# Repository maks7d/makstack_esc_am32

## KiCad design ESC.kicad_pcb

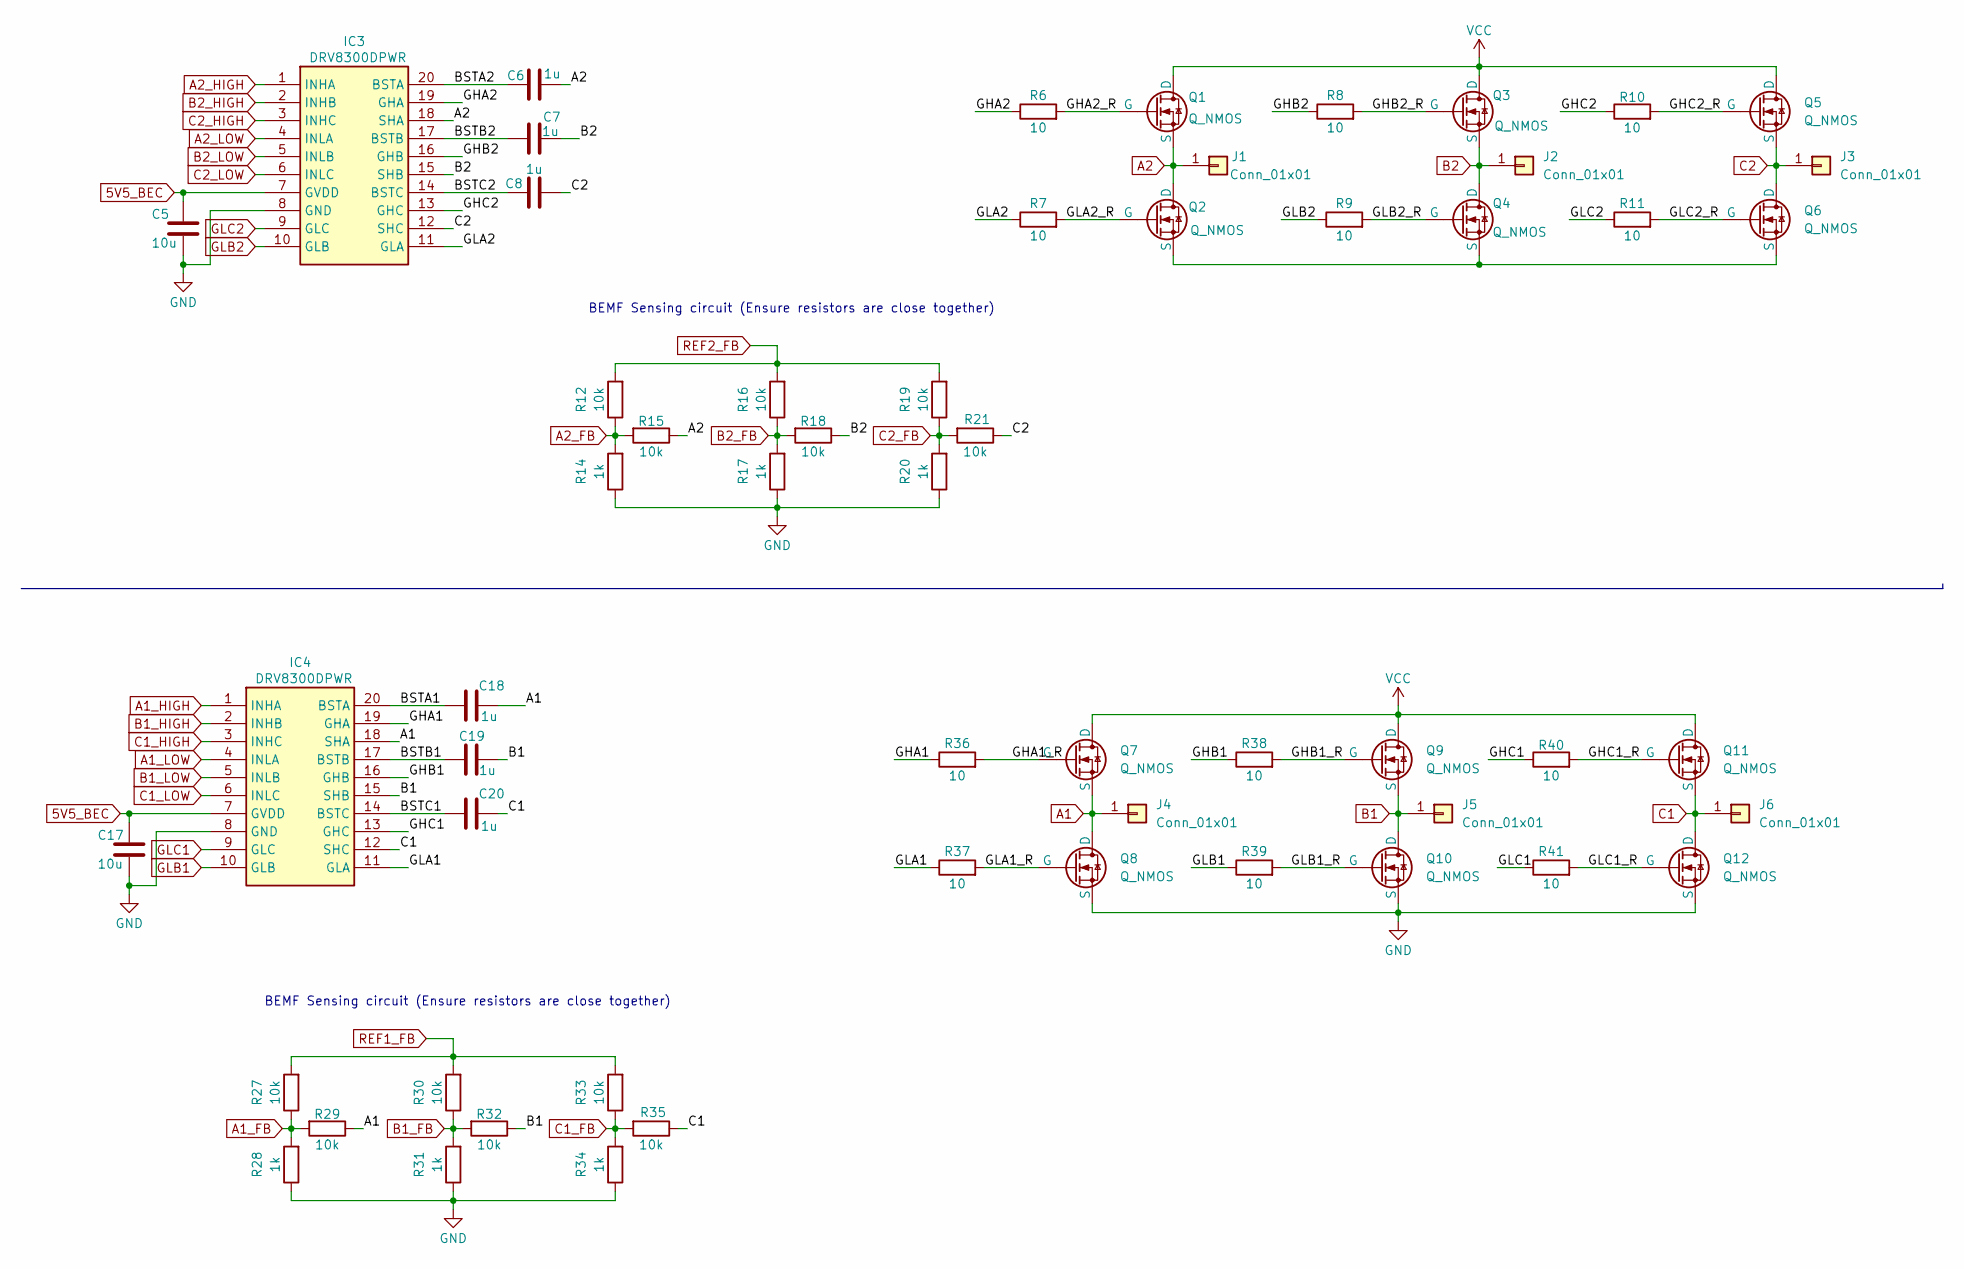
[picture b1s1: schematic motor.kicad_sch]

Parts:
C5, C17: 10u; C_0402_1005Metric
C6, C7, C8, C18, C19, C20: 1u; C_0402_1005Metric
IC3, IC4: DRV8300DPWR; SOP65P640X120-20M; Mouser Part Number 595-DRV8300DPWR
J1, J2, J3, J4, J5, J6: Conn_01x01; TestPoint_Pad_2.0x2.0mm
Q1, Q2, Q3, Q4, Q5, Q6, Q7, Q8, Q9, Q10, Q11, Q12: Q_NMOS; TRANS_NTMFS5C628NLT1G
R6, R7, R8, R9, R10, R11, R36, R37, R38, R39, R40, R41: 10; R_0402_1005Metric
R12, R15, R16, R18, R19, R21, R27, R29, R30, R32, R33, R35: 10k; R_0402_1005Metric
R14, R17, R20, R28, R31, R34: 1k; R_0402_1005Metric

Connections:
5V5_BEC: C5.1, C17.1, IC3.7 (GVDD), IC4.7 (GVDD); also elsewhere on the board
/Motor1-2/BSTA1: C18.1, IC4.20 (BSTA)
/Motor1-2/BSTA2: C6.1, IC3.20 (BSTA)
/Motor1-2/BSTB1: C19.1, IC4.17 (BSTB)
/Motor1-2/BSTB2: C7.1, IC3.17 (BSTB)
/Motor1-2/BSTC1: C20.1, IC4.14 (BSTC)
/Motor1-2/BSTC2: C8.1, IC3.14 (BSTC)
/Motor1-2/GHA1: IC4.19 (GHA), R36.1
/Motor1-2/GHA1_R: Q7.G, R36.2
/Motor1-2/GHA2: IC3.19 (GHA), R6.1
/Motor1-2/GHA2_R: Q1.G, R6.2
/Motor1-2/GHB1: IC4.16 (GHB), R38.1
/Motor1-2/GHB1_R: Q9.G, R38.2
/Motor1-2/GHB2: IC3.16 (GHB), R8.1
/Motor1-2/GHB2_R: Q3.G, R8.2
/Motor1-2/GHC1: IC4.13 (GHC), R40.1
/Motor1-2/GHC1_R: Q11.G, R40.2
/Motor1-2/GHC2: IC3.13 (GHC), R10.1
/Motor1-2/GHC2_R: Q5.G, R10.2
/Motor1-2/GLA1: IC4.11 (GLA), R37.1
/Motor1-2/GLA1_R: Q8.G, R37.2
/Motor1-2/GLA2: IC3.11 (GLA), R7.1
/Motor1-2/GLA2_R: Q2.G, R7.2
/Motor1-2/GLB1_R: Q10.G, R39.2
/Motor1-2/GLB2_R: Q4.G, R9.2
/Motor1-2/GLC1_R: Q12.G, R41.2
/Motor1-2/GLC2_R: Q6.G, R11.2
A1: C18.2, IC4.18 (SHA), J4.1, Q7.S, Q8.D, R29.1
A1_FB: R27.1, R28.2, R29.2; also elsewhere on the board
A1_HIGH: IC4.1 (INHA); also elsewhere on the board
A1_LOW: IC4.4 (INLA); also elsewhere on the board
A2: C6.2, IC3.18 (SHA), J1.1, Q1.S, Q2.D, R15.1
A2_FB: R12.1, R14.2, R15.2; also elsewhere on the board
A2_HIGH: IC3.1 (INHA); also elsewhere on the board
A2_LOW: IC3.4 (INLA); also elsewhere on the board
B1: C19.2, IC4.15 (SHB), J5.1, Q9.S, Q10.D, R32.1
B1_FB: R30.1, R31.2, R32.2; also elsewhere on the board
B1_HIGH: IC4.2 (INHB); also elsewhere on the board
B1_LOW: IC4.5 (INLB); also elsewhere on the board
B2: C7.2, IC3.15 (SHB), J2.1, Q3.S, Q4.D, R18.1
B2_FB: R16.1, R17.2, R18.2; also elsewhere on the board
B2_HIGH: IC3.2 (INHB); also elsewhere on the board
B2_LOW: IC3.5 (INLB); also elsewhere on the board
C1: C20.2, IC4.12 (SHC), J6.1, Q11.S, Q12.D, R35.1
C1_FB: R33.1, R34.2, R35.2; also elsewhere on the board
C1_HIGH: IC4.3 (INHC); also elsewhere on the board
C1_LOW: IC4.6 (INLC); also elsewhere on the board
C2: C8.2, IC3.12 (SHC), J3.1, Q5.S, Q6.D, R21.1
C2_FB: R19.1, R20.2, R21.2; also elsewhere on the board
C2_HIGH: IC3.3 (INHC); also elsewhere on the board
C2_LOW: IC3.6 (INLC); also elsewhere on the board
GLB1: IC4.10 (GLB), R39.1
GLB2: IC3.10 (GLB), R9.1
GLC1: IC4.9 (GLC), R41.1
GLC2: IC3.9 (GLC), R11.1
GND: C5.2, C17.2, IC3.8 (GND), IC4.8 (GND), Q8.S, Q10.S, Q12.S, R14.1, R17.1, R20.1, R28.1, R31.1, R34.1; also elsewhere on the board
unnamed: Q2.S, Q4.S, Q6.S
REF1_FB: R27.2, R30.2, R33.2; also elsewhere on the board
REF2_FB: R12.2, R16.2, R19.2
VCC: Q1.D, Q3.D, Q5.D, Q7.D, Q9.D, Q11.D; also elsewhere on the board

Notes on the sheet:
BEMF Sensing circuit (Ensure resistors are close together)

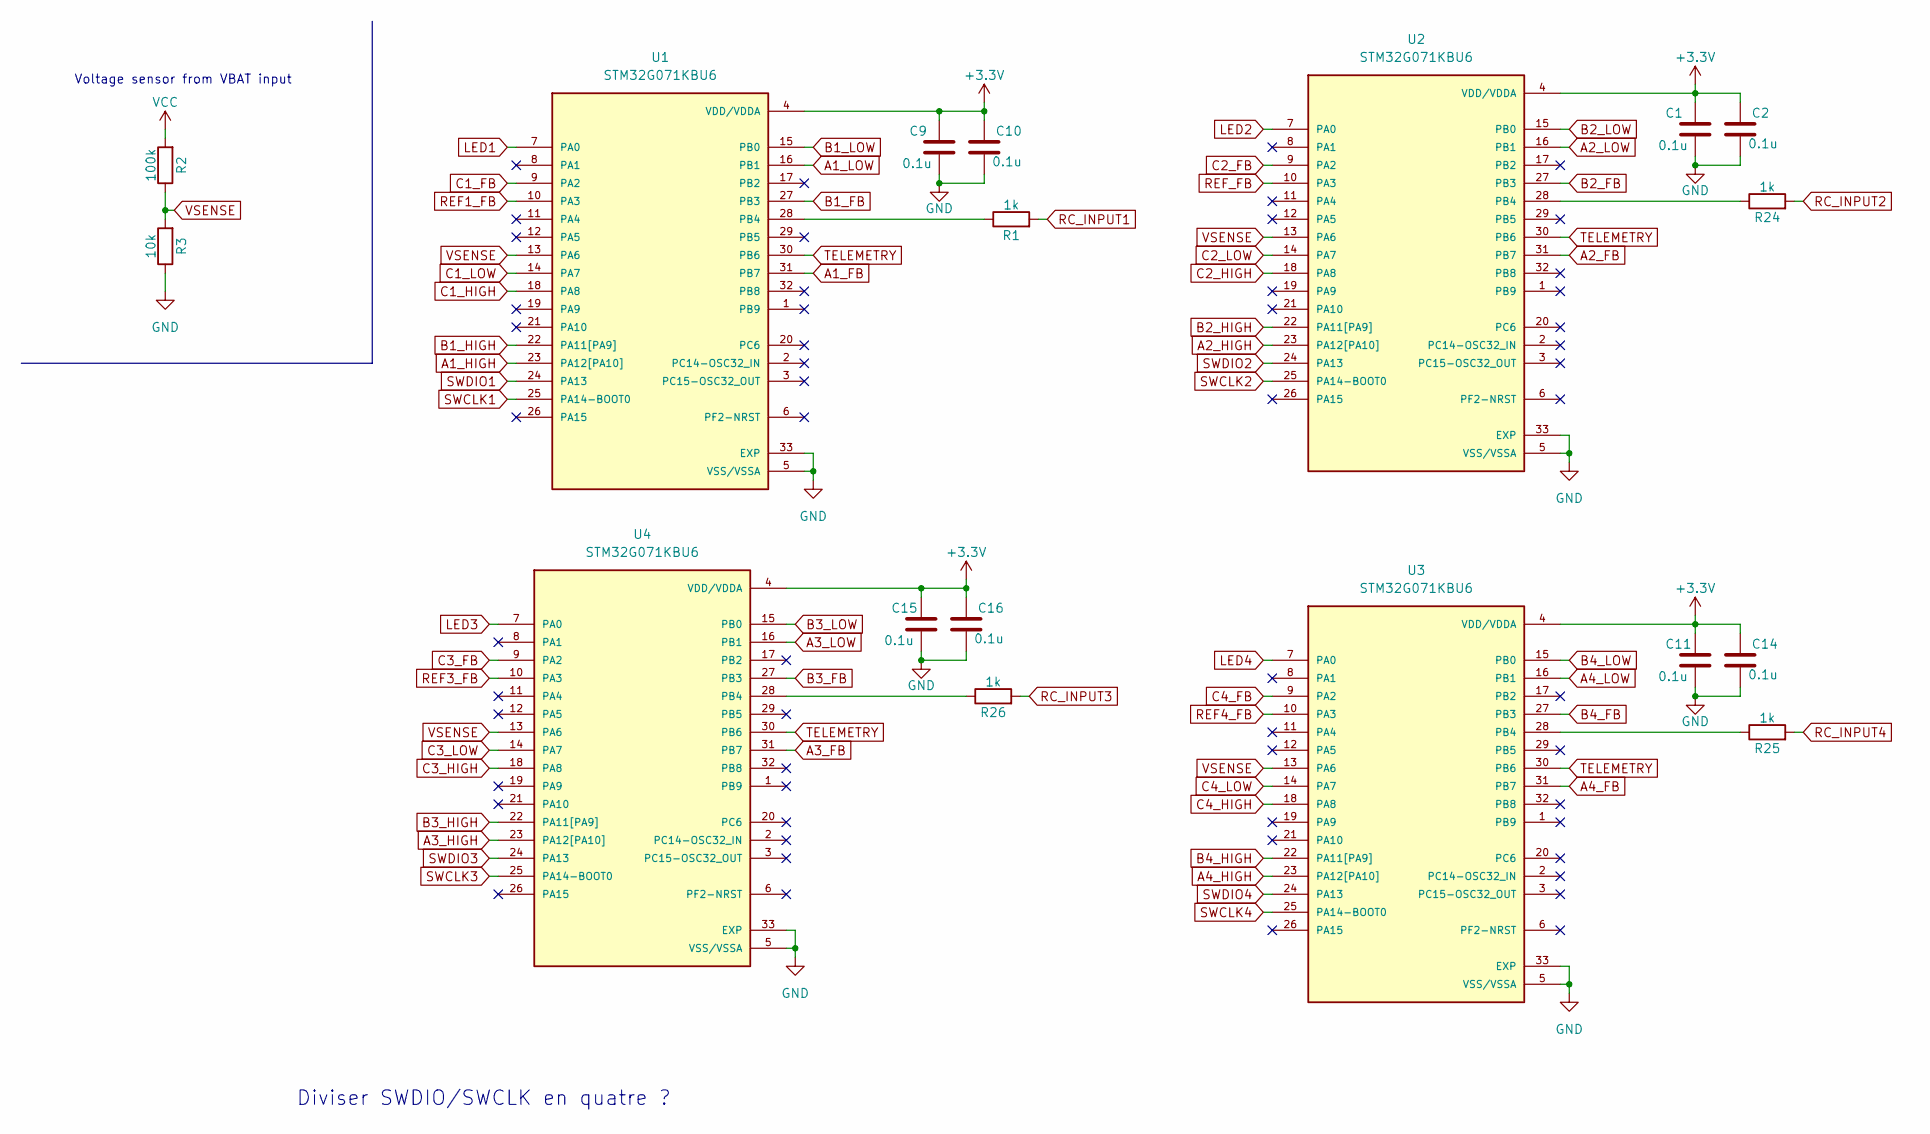
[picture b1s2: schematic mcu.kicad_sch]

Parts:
C1, C2, C9, C10, C11, C14, C15, C16: 0.1u; C_0402_1005Metric
R1, R24, R25, R26: 1k; R_0402_1005Metric
R2: 100k; R_0402_1005Metric
R3: 10k; R_0402_1005Metric
U1, U2, U3, U4: STM32G071KBU6; QFN50P500X500X60-33N; PARTREV 2

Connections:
+3.3V: C1.1, C2.1, C9.1, C10.1, C11.1, C14.1, C15.1, C16.1, U1.4 (VDD/VDDA), U2.4 (VDD/VDDA), U3.4 (VDD/VDDA), U4.4 (VDD/VDDA); also elsewhere on the board
A1_FB: U1.31 (PB7); also elsewhere on the board
A1_HIGH: U1.23 (PA12[PA10]); also elsewhere on the board
A1_LOW: U1.16 (PB1); also elsewhere on the board
A2_FB: U2.31 (PB7); also elsewhere on the board
A2_HIGH: U2.23 (PA12[PA10]); also elsewhere on the board
A2_LOW: U2.16 (PB1); also elsewhere on the board
A3_FB: U4.31 (PB7); also elsewhere on the board
A3_HIGH: U4.23 (PA12[PA10]); also elsewhere on the board
A3_LOW: U4.16 (PB1); also elsewhere on the board
A4_FB: U3.31 (PB7); also elsewhere on the board
A4_HIGH: U3.23 (PA12[PA10]); also elsewhere on the board
A4_LOW: U3.16 (PB1); also elsewhere on the board
B1_FB: U1.27 (PB3); also elsewhere on the board
B1_HIGH: U1.22 (PA11[PA9]); also elsewhere on the board
B1_LOW: U1.15 (PB0); also elsewhere on the board
B2_FB: U2.27 (PB3); also elsewhere on the board
B2_HIGH: U2.22 (PA11[PA9]); also elsewhere on the board
B2_LOW: U2.15 (PB0); also elsewhere on the board
B3_FB: U4.27 (PB3); also elsewhere on the board
B3_HIGH: U4.22 (PA11[PA9]); also elsewhere on the board
B3_LOW: U4.15 (PB0); also elsewhere on the board
B4_FB: U3.27 (PB3); also elsewhere on the board
B4_HIGH: U3.22 (PA11[PA9]); also elsewhere on the board
B4_LOW: U3.15 (PB0); also elsewhere on the board
C1_FB: U1.9 (PA2); also elsewhere on the board
C1_HIGH: U1.18 (PA8); also elsewhere on the board
C1_LOW: U1.14 (PA7); also elsewhere on the board
C2_FB: U2.9 (PA2); also elsewhere on the board
C2_HIGH: U2.18 (PA8); also elsewhere on the board
C2_LOW: U2.14 (PA7); also elsewhere on the board
C3_FB: U4.9 (PA2); also elsewhere on the board
C3_HIGH: U4.18 (PA8); also elsewhere on the board
C3_LOW: U4.14 (PA7); also elsewhere on the board
C4_FB: U3.9 (PA2)
C4_HIGH: U3.18 (PA8); also elsewhere on the board
C4_LOW: U3.14 (PA7); also elsewhere on the board
GND: C1.2, C2.2, C9.2, C10.2, C11.2, C14.2, C15.2, C16.2, R3.1, U1.5 (VSS/VSSA), U1.33 (EXP), U2.5 (VSS/VSSA), U2.33 (EXP), U3.5 (VSS/VSSA), U3.33 (EXP), U4.5 (VSS/VSSA), U4.33 (EXP); also elsewhere on the board
LED1: U1.7 (PA0)
LED2: U2.7 (PA0)
LED3: U4.7 (PA0)
LED4: U3.7 (PA0)
unnamed: R1.1, U1.28 (PB4)
unnamed: R24.1, U2.28 (PB4)
unnamed: R25.1, U3.28 (PB4)
unnamed: R26.1, U4.28 (PB4)
RC_INPUT1: R1.2; also elsewhere on the board
RC_INPUT2: R24.2; also elsewhere on the board
RC_INPUT3: R26.2; also elsewhere on the board
RC_INPUT4: R25.2; also elsewhere on the board
REF1_FB: U1.10 (PA3); also elsewhere on the board
REF3_FB: U4.10 (PA3); also elsewhere on the board
REF4_FB: U3.10 (PA3); also elsewhere on the board
REF_FB: U2.10 (PA3)
SWCLK1: U1.25 (PA14-BOOT0); also elsewhere on the board
SWCLK2: U2.25 (PA14-BOOT0); also elsewhere on the board
SWCLK3: U4.25 (PA14-BOOT0); also elsewhere on the board
SWCLK4: U3.25 (PA14-BOOT0); also elsewhere on the board
SWDIO1: U1.24 (PA13); also elsewhere on the board
SWDIO2: U2.24 (PA13); also elsewhere on the board
SWDIO3: U4.24 (PA13); also elsewhere on the board
SWDIO4: U3.24 (PA13); also elsewhere on the board
TELEMETRY: U1.30 (PB6), U2.30 (PB6), U3.30 (PB6), U4.30 (PB6); also elsewhere on the board
VCC: R2.2; also elsewhere on the board
VSENSE: R2.1, R3.2, U1.13 (PA6), U2.13 (PA6), U3.13 (PA6), U4.13 (PA6)

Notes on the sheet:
Diviser SWDIO/SWCLK en quatre ?
Voltage sensor from VBAT input

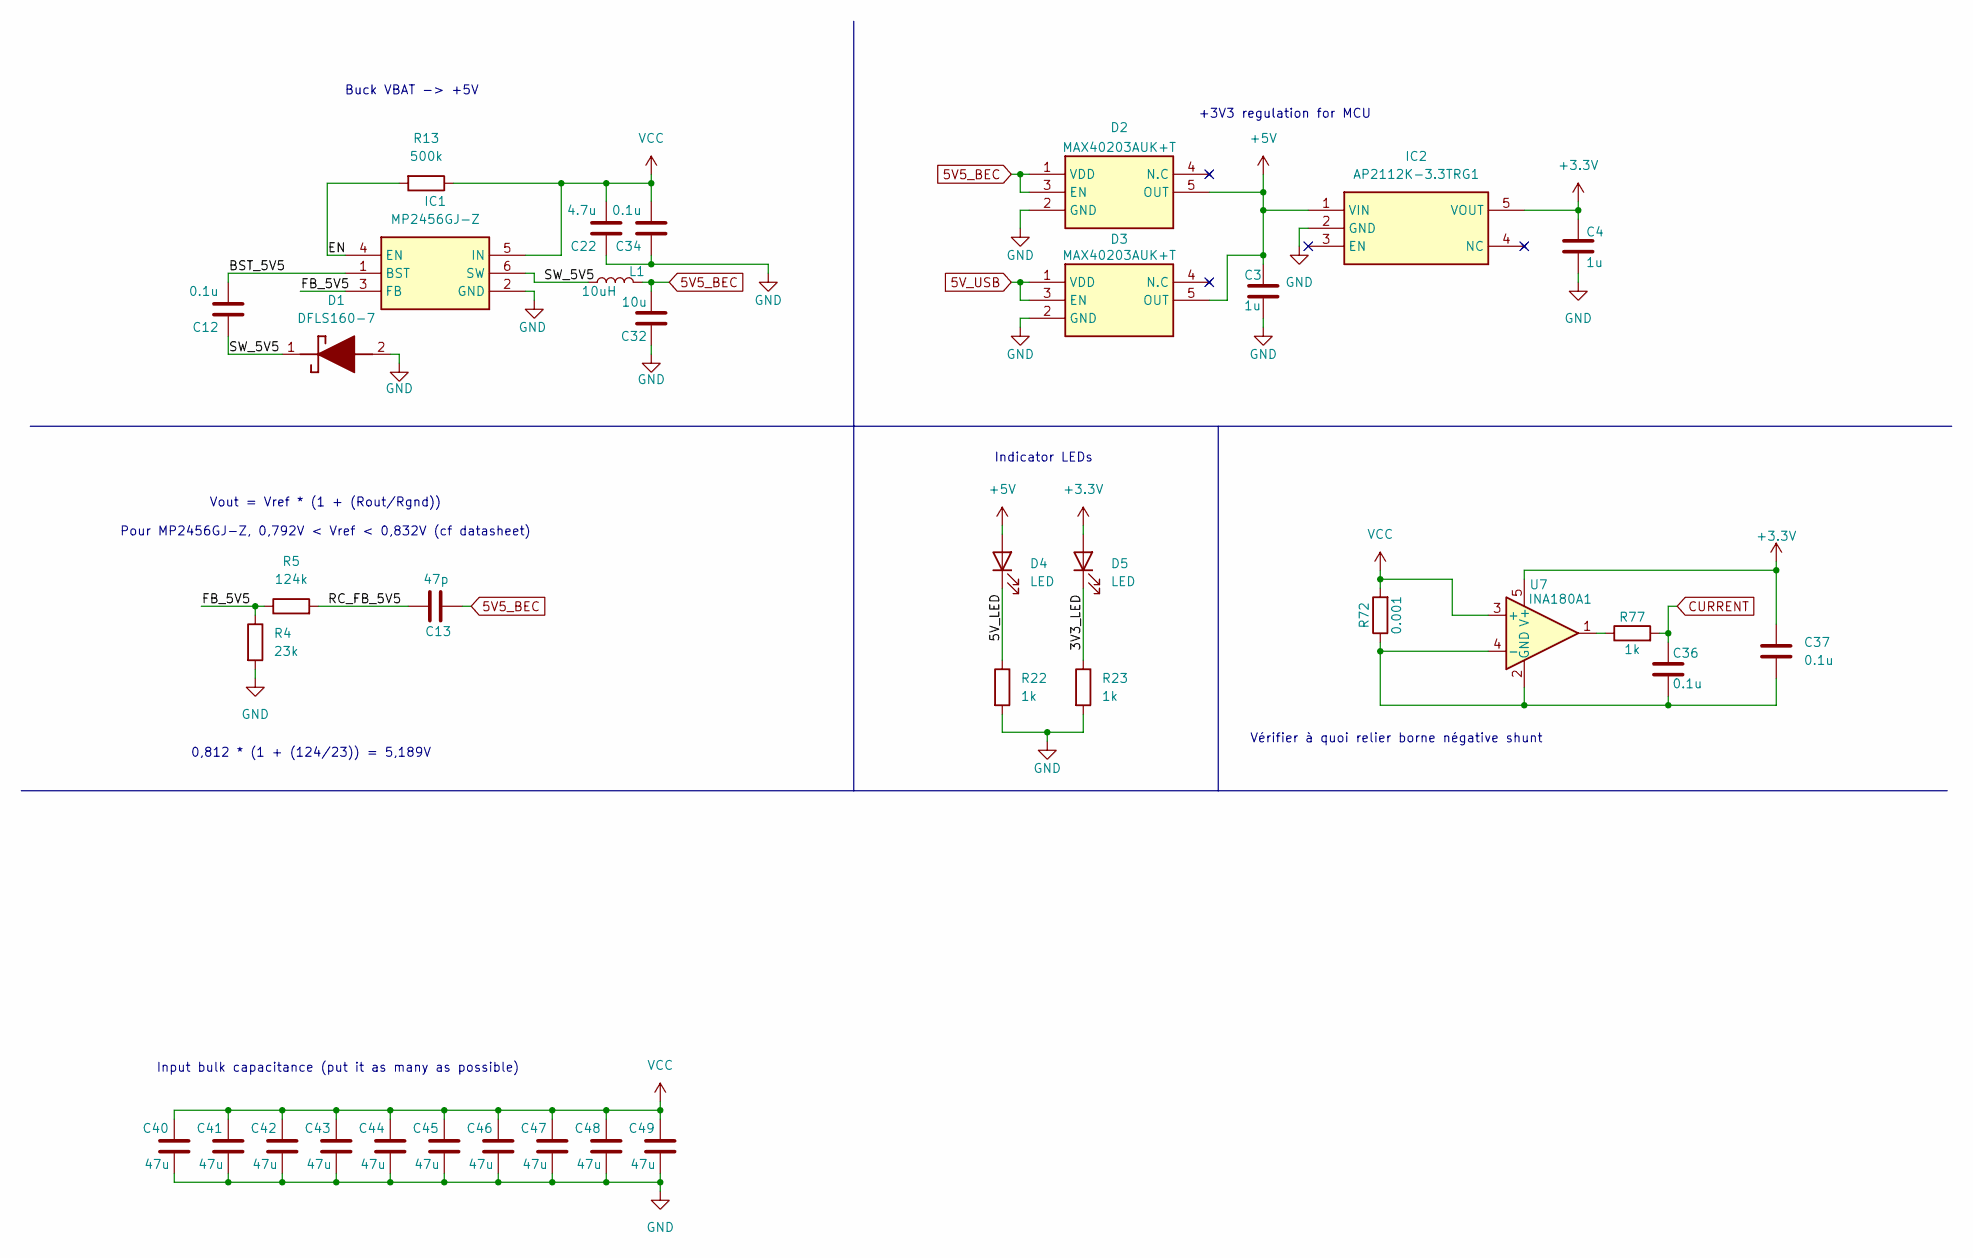
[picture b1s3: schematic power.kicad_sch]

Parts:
C3, C4: 1u; C_0402_1005Metric; Manufacturer_Part_Number GRM155R61H105KE05D; LCSC Part Name C1518208
C12, C34: 0.1u; C_0402_1005Metric; Manufacturer_Part_Number GRM188R6YA106MA73D; LCSC Part Name C194427
C13: 47p; C_0402_1005Metric; Manufacturer_Part_Number GRM188C61E226ME01D; LCSC Part Name C29519229
C22: 4.7u; C_0402_1005Metric; Manufacturer_Part_Number GRM188R6YA106MA73D; LCSC Part Name C194427
C32: 10u; C_0603_1608Metric; Manufacturer_Part_Number GRM188C61E226ME01D; LCSC Part Name C29519229
C36, C37: 0.1u; C_0402_1005Metric
C40, C41, C42, C43, C44, C45, C46, C47, C48, C49: 47u; C_0805_2012Metric; Manufacturer_Part_Number GRM188C61E226ME01D; LCSC Part Name C29519229
D1: DFLS160-7; DFLS1607; Mouser Part Number 621-DFLS160-F
D2, D3: MAX40203AUK+T; SOT95P280X145-5N; Mouser Part Number 700-MAX40203AUK+T
D4, D5: LED; LED_L135-G525003500000
IC1: MP2456GJ-Z; SOP95P280X100-6M; Mouser Part Number 946-MP2456GJ-Z
IC2: AP2112K-3.3TRG1; SOT95P285X140-5M; Mouser Part Number 621-AP2112K-3.3TRG1
L1: 10uH; L_1210_3225Metric; Manufacturer_Part_Number XRTC322512S100MBCA; LCSC Part Name C39846661
R4: 23k; R_0402_1005Metric; Manufacturer_Part_Number RC0402FR-077K68L; LCSC Part Name C155695
R5: 124k; R_0402_1005Metric; Manufacturer_Part_Number 0402WGF4122TCE; LCSC Part Name C26978
R13: 500k; R_0402_1005Metric; Manufacturer_Part_Number RC0402FR-071ML; LCSC Part Name C138033
R22, R23: 1k; R_0402_1005Metric; Manufacturer_Part_Number RC0402FR-071ML; LCSC Part Name C138033
R72: 0.001; R_2512_6332Metric
R77: 1k; R_0402_1005Metric
U7: INA180A1; SOT-23-5

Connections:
5V5_BEC: C13.1, C32.2, D2.1 (VDD), D2.3 (EN), L1.2; also elsewhere on the board
5V_USB: D3.1 (VDD), D3.3 (EN)
+3.3V: C4.1, C37.1, D5.2 (A), IC2.5 (VOUT), U7.5 (V+); also elsewhere on the board
+5V: C3.1, D2.5 (OUT), D3.5 (OUT), D4.2 (A), IC2.1 (VIN)
/Power/3V3_LED: D5.1 (K), R23.1
/Power/5V_LED: D4.1 (K), R22.1
/Power/BST_5V5: C12.2, IC1.1 (BST)
/Power/EN: IC1.4 (EN), R13.2
/Power/FB_5V5: IC1.3 (FB), R4.1, R5.1
/Power/RC_FB_5V5: C13.2, R5.2
/Power/SW_5V5: C12.1, D1.1 (K), IC1.6 (SW), L1.1
CURRENT: C36.1, R77.2; also elsewhere on the board
GND: C3.2, C4.2, C22.1, C32.1, C34.1, C40.2, C41.2, C42.2, C43.2, C44.2, C45.2, C46.2, C47.2, C48.2, C49.2, D1.2 (A), D2.2 (GND), D3.2 (GND), IC1.2 (GND), IC2.2 (GND), R4.2, R22.2, R23.2; also elsewhere on the board
unnamed: R77.1, U7.1
unnamed: C36.2, C37.2, R72.1, U7.2 (GND), U7.4 (-)
VCC: C22.2, C34.2, C40.1, C41.1, C42.1, C43.1, C44.1, C45.1, C46.1, C47.1, C48.1, C49.1, IC1.5 (IN), R13.1, R72.2, U7.3 (+); also elsewhere on the board

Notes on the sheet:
Input bulk capacitance (put it as many as possible)
Vérifier à quoi relier borne négative shunt
Buck VBAT -> +5V
0,812 * (1 + (124/23)) = 5,189V
+3V3 regulation for MCU
Vout = Vref * (1 + (Rout/Rgnd)) Pour MP2456GJ-Z, 0,792V < Vref < 0,832V (cf datasheet)
Indicator LEDs

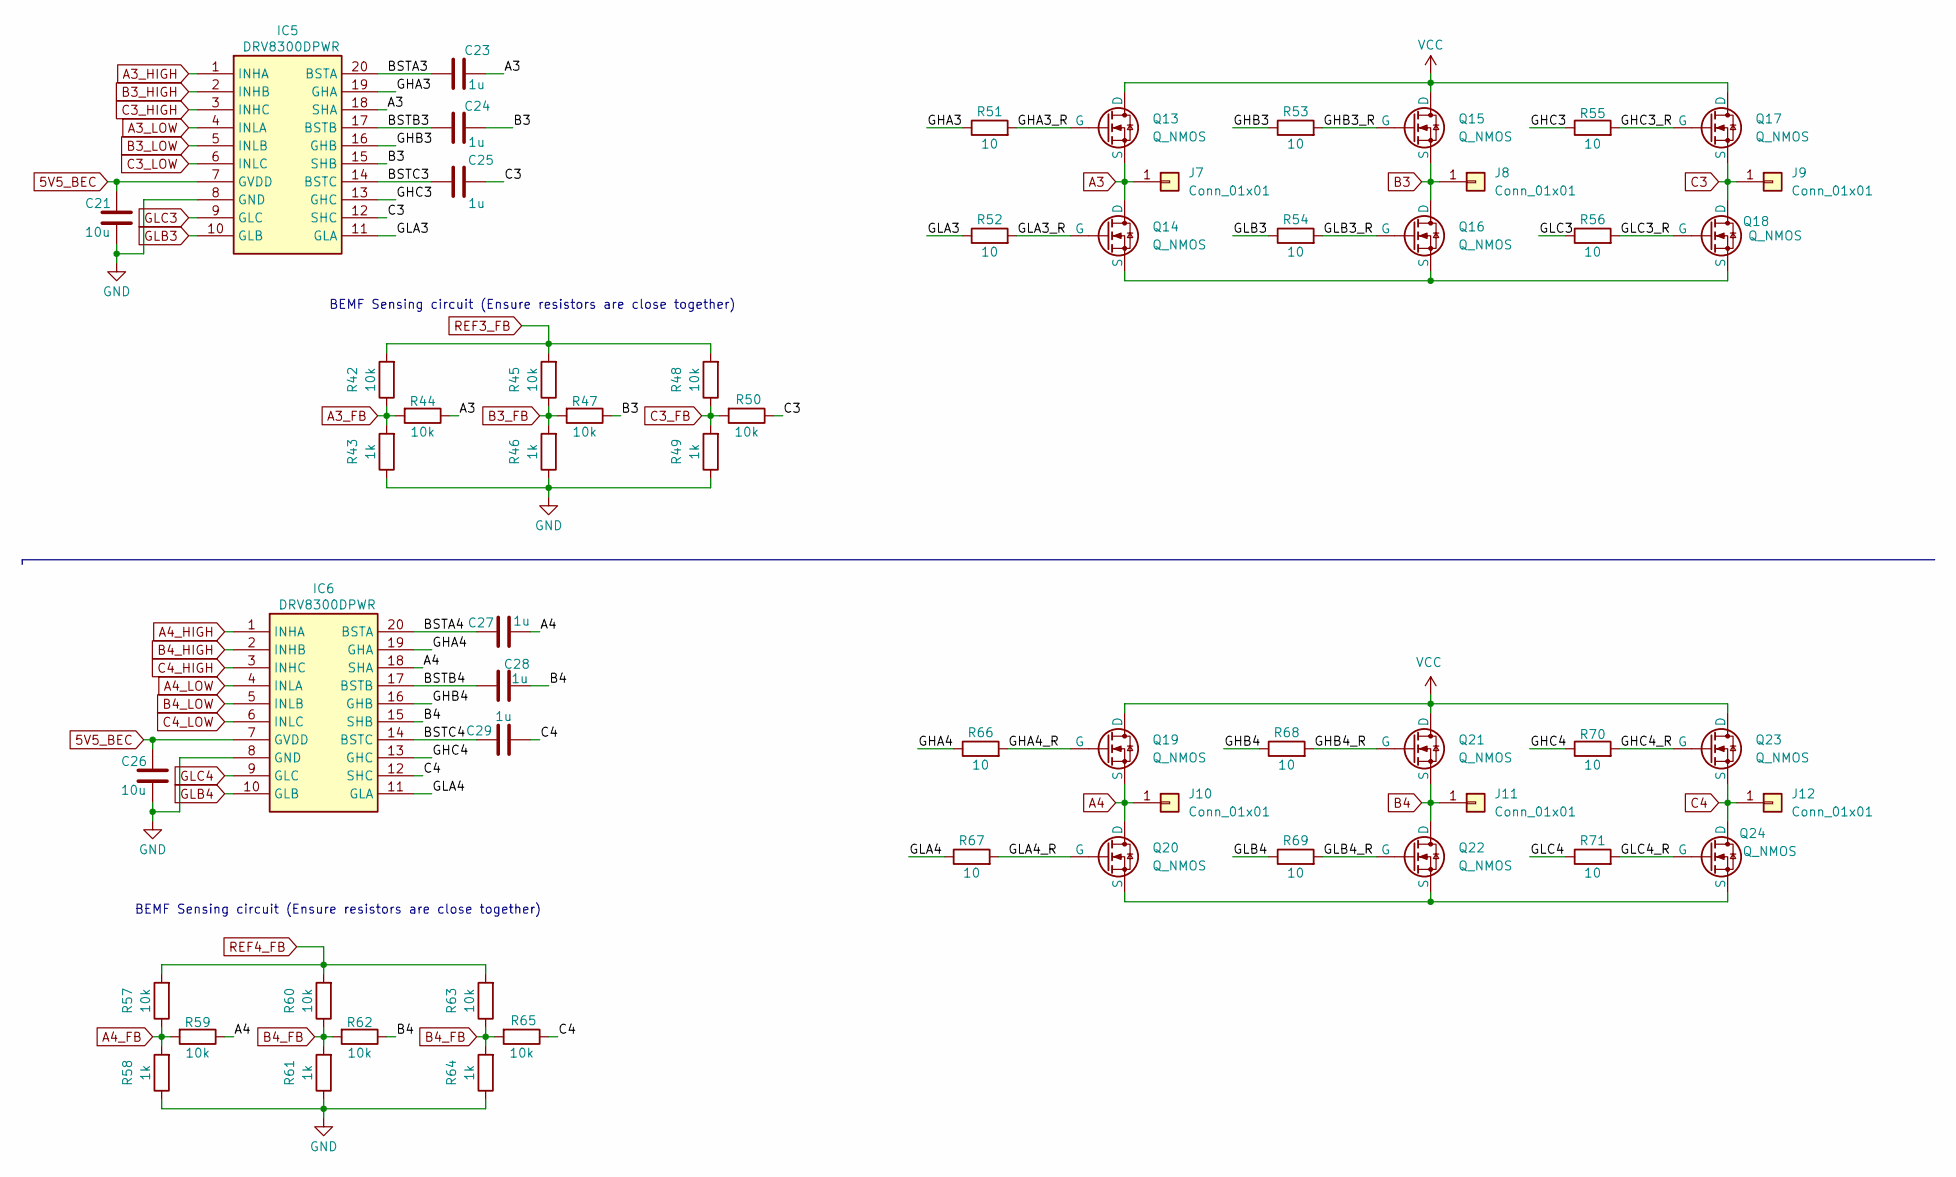
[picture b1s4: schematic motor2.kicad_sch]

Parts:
C21, C26: 10u; C_0402_1005Metric
C23, C24, C25, C27, C28, C29: 1u; C_0402_1005Metric
IC5, IC6: DRV8300DPWR; SOP65P640X120-20M; Mouser Part Number 595-DRV8300DPWR
J7, J8, J9, J10, J11, J12: Conn_01x01; TestPoint_Pad_2.0x2.0mm
Q13, Q14, Q15, Q16, Q17, Q18, Q19, Q20, Q21, Q22, Q23, Q24: Q_NMOS; TRANS_NTMFS5C628NLT1G
R42, R44, R45, R47, R48, R50, R57, R59, R60, R62, R63, R65: 10k; R_0402_1005Metric
R43, R46, R49, R58, R61, R64: 1k; R_0402_1005Metric
R51, R52, R53, R54, R55, R56, R66, R67, R68, R69, R70, R71: 10; R_0402_1005Metric

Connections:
5V5_BEC: C21.1, C26.1, IC5.7 (GVDD), IC6.7 (GVDD); also elsewhere on the board
/Motor3-4/BSTA3: C23.1, IC5.20 (BSTA)
/Motor3-4/BSTA4: C27.1, IC6.20 (BSTA)
/Motor3-4/BSTB3: C24.1, IC5.17 (BSTB)
/Motor3-4/BSTB4: C28.1, IC6.17 (BSTB)
/Motor3-4/BSTC3: C25.1, IC5.14 (BSTC)
/Motor3-4/BSTC4: C29.1, IC6.14 (BSTC)
/Motor3-4/GHA3: IC5.19 (GHA), R51.1
/Motor3-4/GHA3_R: Q13.G, R51.2
/Motor3-4/GHA4: IC6.19 (GHA), R66.1
/Motor3-4/GHA4_R: Q19.G, R66.2
/Motor3-4/GHB3: IC5.16 (GHB), R53.1
/Motor3-4/GHB3_R: Q15.G, R53.2
/Motor3-4/GHB4: IC6.16 (GHB), R68.1
/Motor3-4/GHB4_R: Q21.G, R68.2
/Motor3-4/GHC3: IC5.13 (GHC), R55.1
/Motor3-4/GHC3_R: Q17.G, R55.2
/Motor3-4/GHC4: IC6.13 (GHC), R70.1
/Motor3-4/GHC4_R: Q23.G, R70.2
/Motor3-4/GLA3: IC5.11 (GLA), R52.1
/Motor3-4/GLA3_R: Q14.G, R52.2
/Motor3-4/GLA4: IC6.11 (GLA), R67.1
/Motor3-4/GLA4_R: Q20.G, R67.2
/Motor3-4/GLB3_R: Q16.G, R54.2
/Motor3-4/GLB4_R: Q22.G, R69.2
/Motor3-4/GLC3_R: Q18.G, R56.2
/Motor3-4/GLC4_R: Q24.G, R71.2
A3: C23.2, IC5.18 (SHA), J7.1, Q13.S, Q14.D, R44.1
A3_FB: R42.1, R43.2, R44.2; also elsewhere on the board
A3_HIGH: IC5.1 (INHA); also elsewhere on the board
A3_LOW: IC5.4 (INLA); also elsewhere on the board
A4: C27.2, IC6.18 (SHA), J10.1, Q19.S, Q20.D, R59.1
A4_FB: R57.1, R58.2, R59.2; also elsewhere on the board
A4_HIGH: IC6.1 (INHA); also elsewhere on the board
A4_LOW: IC6.4 (INLA); also elsewhere on the board
B3: C24.2, IC5.15 (SHB), J8.1, Q15.S, Q16.D, R47.1
B3_FB: R45.1, R46.2, R47.2; also elsewhere on the board
B3_HIGH: IC5.2 (INHB); also elsewhere on the board
B3_LOW: IC5.5 (INLB); also elsewhere on the board
B4: C28.2, IC6.15 (SHB), J11.1, Q21.S, Q22.D, R62.1
B4_FB: R60.1, R61.2, R62.2, R63.1, R64.2, R65.2; also elsewhere on the board
B4_HIGH: IC6.2 (INHB); also elsewhere on the board
B4_LOW: IC6.5 (INLB); also elsewhere on the board
C3: C25.2, IC5.12 (SHC), J9.1, Q17.S, Q18.D, R50.1
C3_FB: R48.1, R49.2, R50.2; also elsewhere on the board
C3_HIGH: IC5.3 (INHC); also elsewhere on the board
C3_LOW: IC5.6 (INLC); also elsewhere on the board
C4: C29.2, IC6.12 (SHC), J12.1, Q23.S, Q24.D, R65.1
C4_HIGH: IC6.3 (INHC); also elsewhere on the board
C4_LOW: IC6.6 (INLC); also elsewhere on the board
GLB3: IC5.10 (GLB), R54.1
GLB4: IC6.10 (GLB), R69.1
GLC3: IC5.9 (GLC), R56.1
GLC4: IC6.9 (GLC), R71.1
GND: C21.2, C26.2, IC5.8 (GND), IC6.8 (GND), R43.1, R46.1, R49.1, R58.1, R61.1, R64.1; also elsewhere on the board
unnamed: Q14.S, Q16.S, Q18.S
unnamed: Q20.S, Q22.S, Q24.S
REF3_FB: R42.2, R45.2, R48.2; also elsewhere on the board
REF4_FB: R57.2, R60.2, R63.2; also elsewhere on the board
VCC: Q13.D, Q15.D, Q17.D, Q19.D, Q21.D, Q23.D; also elsewhere on the board

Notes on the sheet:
BEMF Sensing circuit (Ensure resistors are close together)

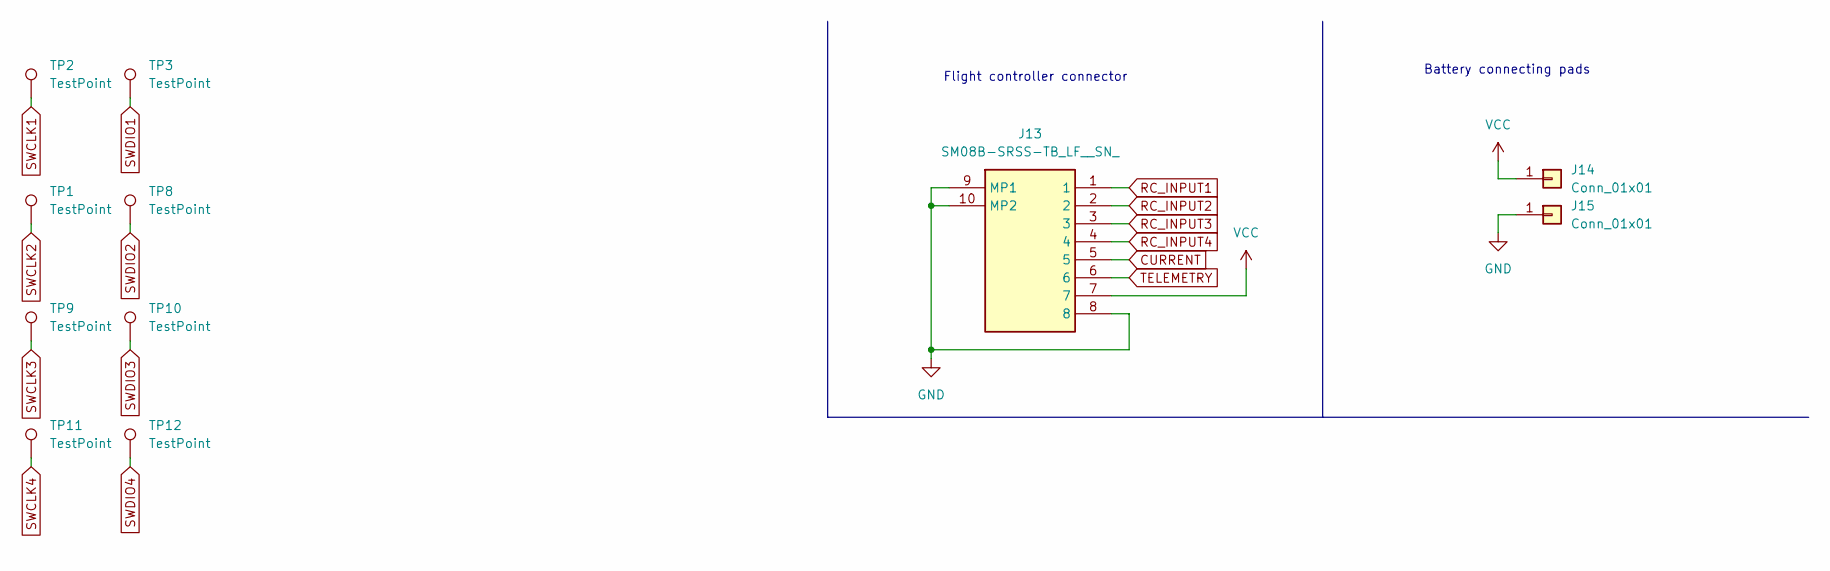
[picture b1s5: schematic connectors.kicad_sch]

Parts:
J13: SM08B-SRSS-TB_LF__SN_; SM08BSRSSTBLFSN; Mouser Part Number N/A
J14, J15: Conn_01x01; TestPoint_Pad_4.0x4.0mm
TP1, TP2, TP3, TP8, TP9, TP10, TP11, TP12: TestPoint; TestPoint_Loop_D1.80mm_Drill1.0mm_Beaded

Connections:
CURRENT: J13.5; also elsewhere on the board
GND: J13.8, J13.9 (MP1), J13.10 (MP2), J15.1; also elsewhere on the board
RC_INPUT1: J13.1; also elsewhere on the board
RC_INPUT2: J13.2; also elsewhere on the board
RC_INPUT3: J13.3; also elsewhere on the board
RC_INPUT4: J13.4; also elsewhere on the board
SWCLK1: TP2.1; also elsewhere on the board
SWCLK2: TP1.1; also elsewhere on the board
SWCLK3: TP9.1; also elsewhere on the board
SWCLK4: TP11.1; also elsewhere on the board
SWDIO1: TP3.1; also elsewhere on the board
SWDIO2: TP8.1; also elsewhere on the board
SWDIO3: TP10.1; also elsewhere on the board
SWDIO4: TP12.1; also elsewhere on the board
TELEMETRY: J13.6; also elsewhere on the board
VCC: J13.7, J14.1; also elsewhere on the board

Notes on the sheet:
Battery connecting pads
Flight controller connector

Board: 2 copper layers, 180 parts (0 on the bottom side), 146 nets, no tracks yet.

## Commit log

2026-03-03 Add symbol library table for ESCs
    - Created a new sym-lib-table file to include the ESCs symbol library.
    - Set library name to "ESCs" with type "KiCad" and linked it to the corresponding .kicad_sym file.
2026-03-04 working on schematic
2026-03-05 finished one full channel, still to duplicate this for 4 channels esc
2026-03-06 duplicate mcu and motor gates circuit
2026-03-10 update schematic
2026-03-13 affected footprints
2026-03-14 minor fixes
2026-03-14 placed first components
